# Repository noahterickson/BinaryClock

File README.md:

BinaryClock
===========

A binary clock design

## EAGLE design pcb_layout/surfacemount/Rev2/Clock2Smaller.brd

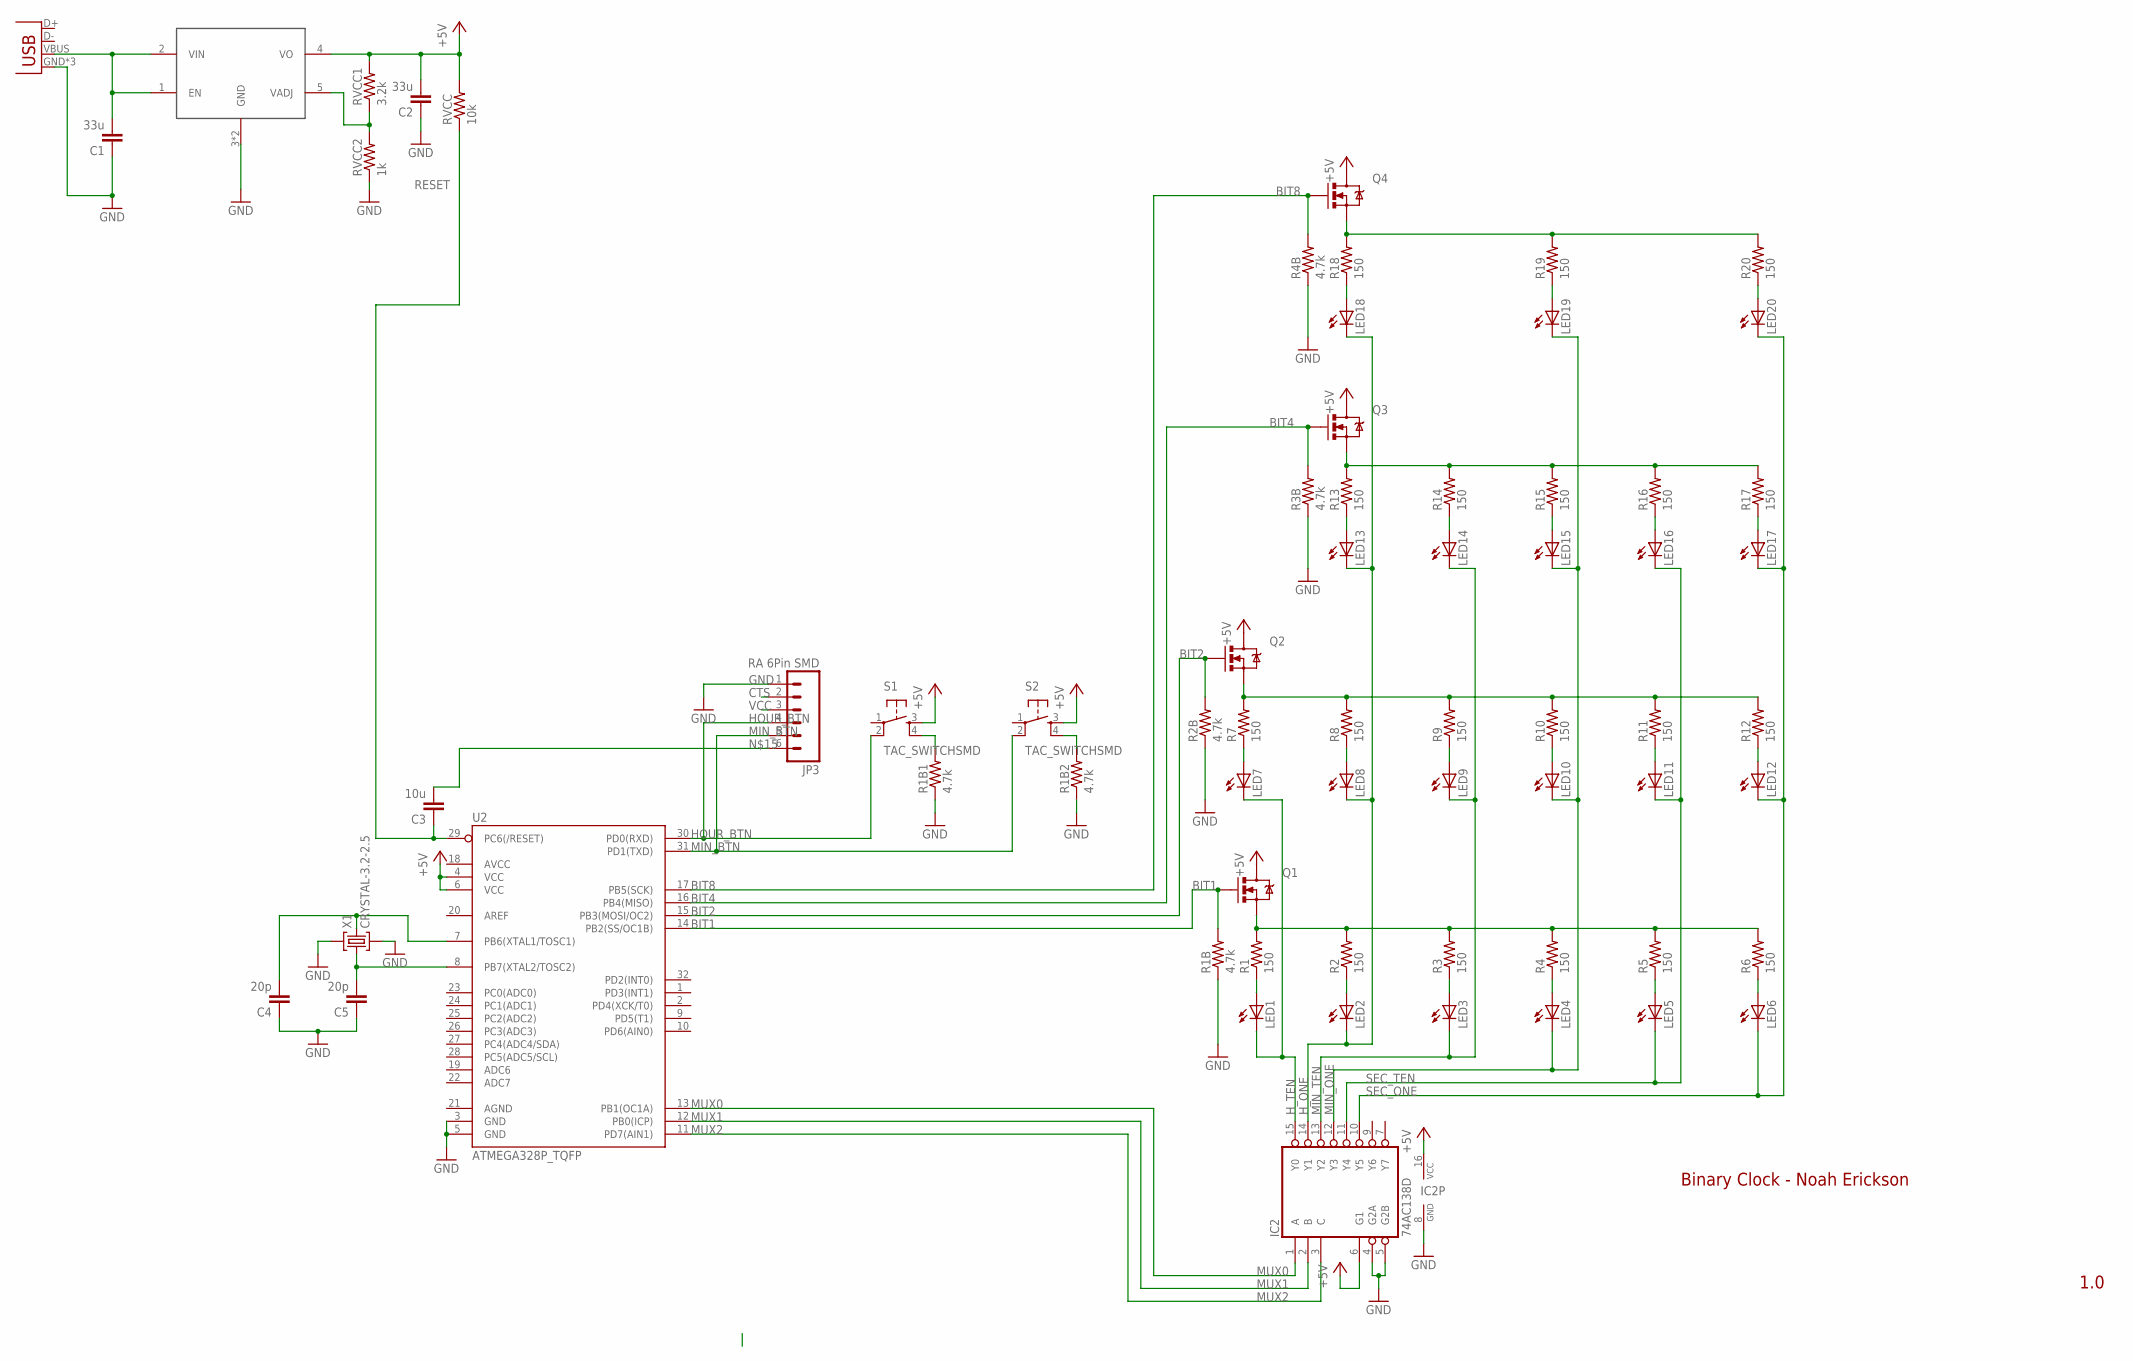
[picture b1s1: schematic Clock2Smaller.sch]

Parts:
C1, C2: 33u; C0805
C3: 10u; C0805
C4, C5: 20p; C0805
IC2: 74AC138D; SO16
JP1: USB-MICROB
JP3: RA 6Pin SMD; 1X06-SMD
LED1, LED2, LED3, LED4, LED5, LED6, LED7, LED8, LED9, LED10, LED11, LED12, LED13, LED14, LED15, LED16, LED17, LED18, LED19, LED20: LEDSML0805; SML0805
Q1, Q2, Q3, Q4: MOSFET-NCHANNELBSS138; SOT23-3
R1, R2, R3, R4, R5, R6, R7, R8, R9, R10, R11, R12, R13, R14, R15, R16, R17, R18, R19, R20: 150; R0805
R1B, R1B1, R1B2, R2B, R3B, R4B: 4.7k; R0805
RVCC: 10k; R0805
RVCC1: 3.2k; R0805
RVCC2: 1k; R0805
S1, S2: TAC_SWITCHSMD; TACTILE-SWITCH-SMD
U2: ATMEGA328P_TQFP; TQFP32-08
U$1: TLF1963; DPAK
X1: CRYSTAL-3.2-2.5

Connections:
+5V: C2.2, IC2.6 (G1), IC2.16 (VCC), Q1.3 (D), Q2.3 (D), Q3.3 (D), Q4.3 (D), RVCC.2, RVCC1.2, S1.3, S2.3, U2.4 (VCC), U2.6 (VCC), U$1.4 (VO)
BIT1: Q1.1 (G), R1B.2, U2.14 (PB2(SS/OC1B))
BIT2: Q2.1 (G), R2B.2, U2.15 (PB3(MOSI/OC2))
BIT4: Q3.1 (G), R3B.2, U2.16 (PB4(MISO))
BIT8: Q4.1 (G), R4B.2, U2.17 (PB5(SCK))
CTS: JP3.2
GND: C1.1, C2.1, C4.1, C5.1, IC2.4 (G2A), IC2.5 (G2B), IC2.8 (GND), JP1.GND, JP1.MT1 (GND), JP1.MT2 (GND), JP3.1, R1B.1, R1B1.1, R1B2.1, R2B.1, R3B.1, R4B.1, RVCC2.1, U2.3 (GND), U2.5 (GND), U$1.3 (GND), U$1.6 (GND), X1.2 (GND), X1.4 (GND)
HOUR_BTN: JP3.4, S1.2, U2.30 (PD0(RXD))
H_ONE: IC2.14 (Y1), LED2.C, LED8.C, LED13.C, LED18.C
H_TEN: IC2.15 (Y0), LED1.C, LED7.C
MIN_BTN: JP3.5, S2.2, U2.31 (PD1(TXD))
MIN_ONE: IC2.12 (Y3), LED4.C, LED10.C, LED15.C, LED19.C
MIN_TEN: IC2.13 (Y2), LED3.C, LED9.C, LED14.C
MUX0: IC2.1 (A), U2.13 (PB1(OC1A))
MUX1: IC2.2 (B), U2.12 (PB0(ICP))
MUX2: IC2.3 (C), U2.11 (PD7(AIN1))
unnamed: C1.2, JP1.VBUS, U$1.1 (EN), U$1.2 (VIN)
unnamed: C5.2, U2.8 (PB7(XTAL2/TOSC2)), X1.1 (C1)
unnamed: C4.2, U2.7 (PB6(XTAL1/TOSC1)), X1.3 (C2)
unnamed: Q4.2 (S), R18.2, R19.2, R20.2
unnamed: LED1.A, R1.1
unnamed: Q1.2 (S), R1.2, R2.2, R3.2, R4.2, R5.2, R6.2
unnamed: R1B1.2, S1.4
unnamed: R1B2.2, S2.4
unnamed: LED2.A, R2.1
unnamed: RVCC1.1, RVCC2.2, U$1.5 (VADJ)
unnamed: C3.2, JP3.6
unnamed: LED3.A, R3.1
unnamed: LED7.A, R7.1
unnamed: Q2.2 (S), R7.2, R8.2, R9.2, R10.2, R11.2, R12.2
unnamed: LED8.A, R8.1
unnamed: LED13.A, R13.1
unnamed: LED9.A, R9.1
unnamed: Q3.2 (S), R13.2, R14.2, R15.2, R16.2, R17.2
unnamed: LED4.A, R4.1
unnamed: LED5.A, R5.1
unnamed: LED18.A, R18.1
unnamed: LED6.A, R6.1
unnamed: LED10.A, R10.1
unnamed: LED11.A, R11.1
unnamed: LED12.A, R12.1
unnamed: LED14.A, R14.1
unnamed: LED15.A, R15.1
unnamed: LED19.A, R19.1
unnamed: LED16.A, R16.1
unnamed: LED17.A, R17.1
unnamed: LED20.A, R20.1
RESET: C3.1, RVCC.1, U2.29 (PC6(/RESET))
SEC_ONE: IC2.10 (Y5), LED6.C, LED12.C, LED17.C, LED20.C
SEC_TEN: IC2.11 (Y4), LED5.C, LED11.C, LED16.C
VCC: JP3.3

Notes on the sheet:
Binary Clock - Noah Erickson
1.0

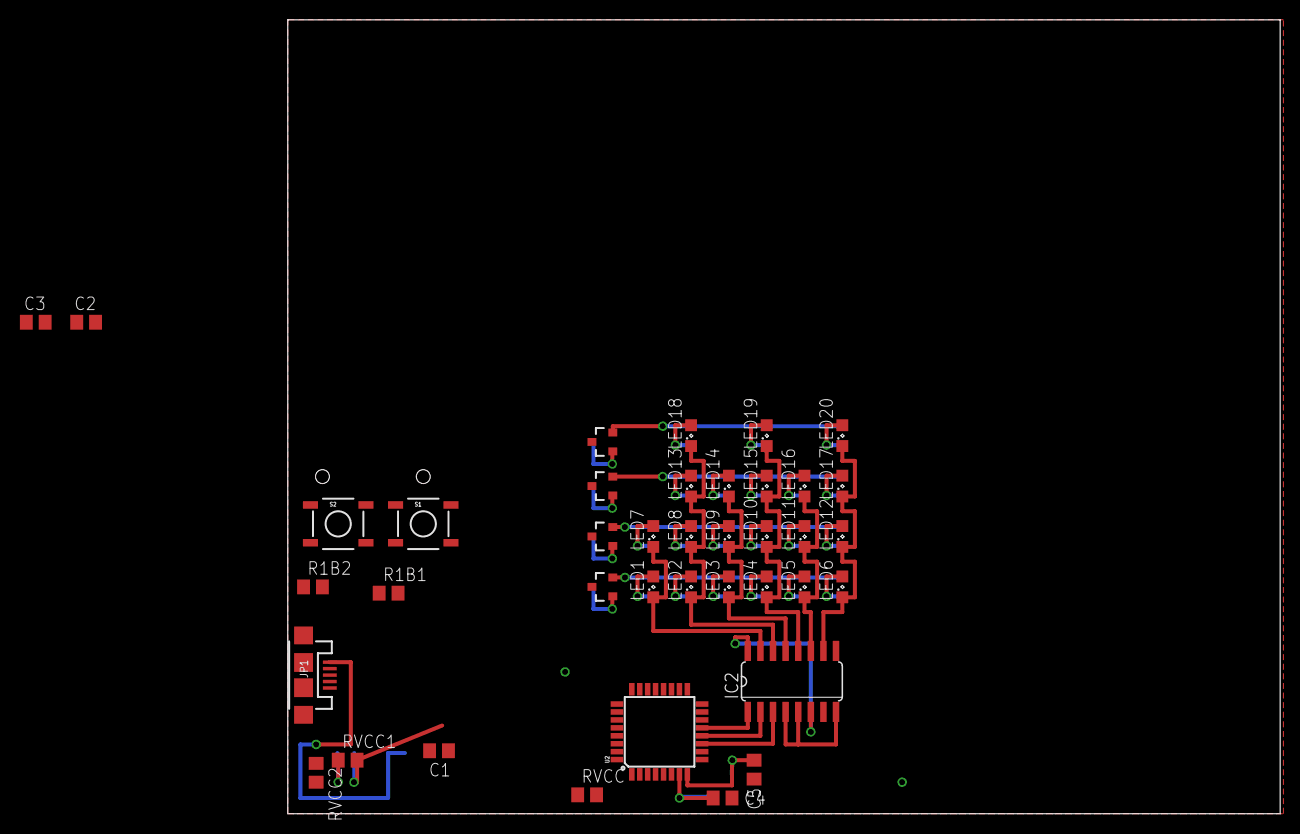
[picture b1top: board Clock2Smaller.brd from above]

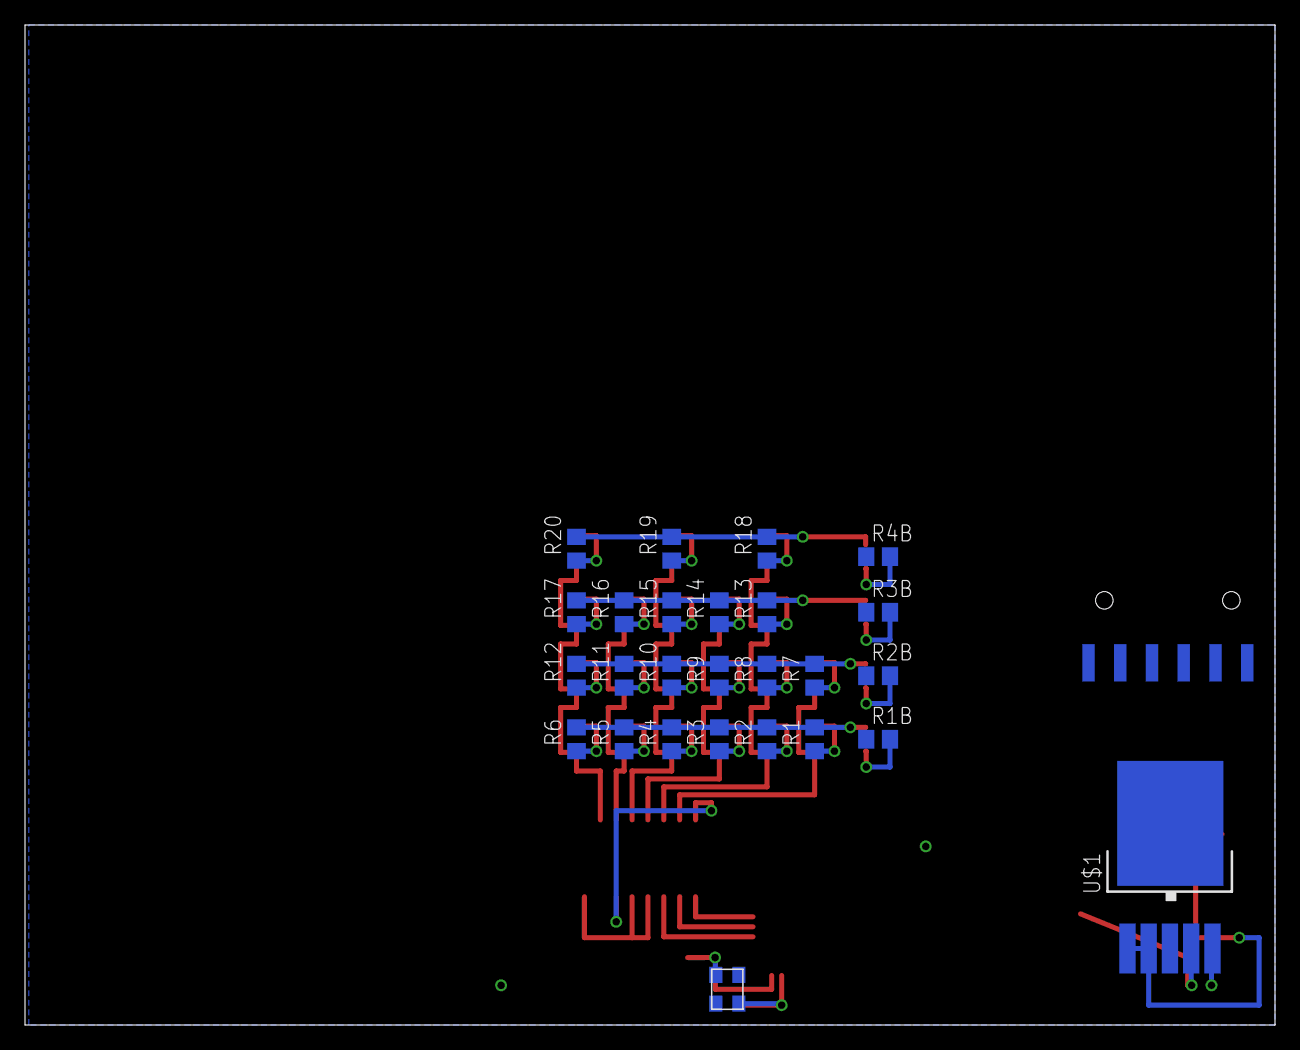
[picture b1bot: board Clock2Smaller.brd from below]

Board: 2 copper layers, 100.0 x 80.0 mm, 66 parts (27 on the bottom side), 49 nets.

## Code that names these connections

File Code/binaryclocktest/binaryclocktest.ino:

/*
Inspired by sbbrain from instructables.com
http://www.instructables.com/id/Full-Binary-Clock/step6/The-Code/
*/

#define mux0 9 //arduino pin 9, atmega pin 15
#define mux1 8 //arduino pin 8, atmega pin 14
#define mux2 7 //arduino pin 7, atmega pin 13

#define bit1 10 //arduino pin 10, atmega pin 16
#define bit2 11 //arduino pin 11, atmega pin 17
#define bit4 12 //arduino pin 12, atmega pin 18
#define bit8 13 //arduino pin 13, atmega pin 19
#define hourButton 2 //arduino pin 0, atmega pin 2
#define minButton 3 //arduino pin 1, atmega pin 3

#include <avr/interrupt.h>


// Function that printf and related will use to print
int serial_putchar(char c, FILE* f) {
    if (c == '\n') serial_putchar('\r', f);
    return Serial.write(c) == 1? 0 : 1;
}

FILE serial_stdout;

void setup(){
    Serial.begin(9600);

    // Set up stdout
    fdev_setup_stream(&serial_stdout, serial_putchar, NULL, _FDEV_SETUP_WRITE);
    stdout = &serial_stdout;

  // put your setup code here, to run once:
  // Enable global interrupts
  SREG |= (1 << 7);
  // Interrupt on rising edge for pins 1,0 (pg. 71)
  EICRA |= (1 << ISC11) | (1 << ISC10) | (ISC01) | (ISC00);
  // Enable interrupts on INT0,INT1 (pins 3,4)
  EIMSK |= (1 << INT1) | (1 << INT0);
  
  Serial.begin(9600);
  
  pinMode(hourButton, INPUT);
  pinMode(minButton, INPUT);
  pinMode(mux0, OUTPUT);
  pinMode(mux1, OUTPUT);
  pinMode(mux2, OUTPUT);
  pinMode(bit1, OUTPUT);
  pinMode(bit2, OUTPUT);
  pinMode(bit4, OUTPUT);
  pinMode(bit8, OUTPUT);
}

void mux(int muxa2, int muxa1, int muxa0){
  digitalWrite(mux0, muxa0);
  digitalWrite(mux1, muxa1);
  digitalWrite(mux2, muxa2);
  
}

int secOne=1, minOne=3, hourOne=0;
int secTen=1, minTen=2, hourTen=0;
int configTime = 1000; //260 seems about right for simulation, 1000 for circuit?

ISR(INT0_vect) {
  hourOne++;
}

ISR(INT1_vect) {
  minOne++;
}

void columns(int columnNum)
{
  byte one;
  byte two;
  byte four;
  byte eight;
  
  switch (columnNum) {
  case 0: //for secOnes
      if (secOne == 1 || secOne == 3 || secOne == 5 || secOne == 7 || secOne == 9) {
        one = HIGH;
      }
      else {
        one = LOW;
      }
      if (secOne == 2 || secOne == 3 || secOne == 6 || secOne == 7) {
        two = HIGH;
      }
      else {
        two = LOW;
      }
      if (secOne == 4 || secOne == 5 || secOne == 6 || secOne == 7) {
        four = HIGH;
      }
      else {
        four = LOW;
      }
      if (secOne == 8 || secOne == 9) {
        eight = HIGH;
      }
      else {
        eight = LOW;
      }
      if (secOne == 0) {
        one = LOW;
        two = LOW;
        four = LOW;
        eight = LOW;
      }
      row(one,two,four,eight);
      break;
  case 1: //for secTens
      if (secTen == 1 || secTen == 3 || secTen == 5 || secTen == 7 || secTen == 9) {
        one = HIGH;
      }
      else {
        one = LOW;
      }
      if (secTen == 2 || secTen == 3 || secTen == 6 || secTen == 7) {
        two = HIGH;
      }
      else {
        two = LOW;
      }
      if (secTen == 4 || secTen == 5 || secTen == 6 || secTen == 7) {
        four = HIGH;
      }
      else {
        four = LOW;
      }
      if (secTen == 8 || secTen == 9) {
        eight = HIGH;
      }
      else {
        eight = LOW;
      }
      if (secTen == 0) {
        one = LOW;
        two = LOW;
        four = LOW;
        eight = LOW;
      }
      row(one,two,four,eight);
      break;
  case 2: //for minOnes
      if (minOne == 1 || minOne == 3 || minOne == 5 || minOne == 7 || minOne == 9) {
        one = HIGH;
      }
      else {
        one = LOW;
      }
      if (minOne == 2 || minOne == 3 || minOne == 6 || minOne == 7) {
        two = HIGH;
      }
      else {
        two = LOW;
      }
      if (minOne == 4 || minOne == 5 || minOne == 6 || minOne == 7) {
        four = HIGH;
      }
      else {
        four = LOW;
      }
      if (minOne == 8 || minOne == 9) {
        eight = HIGH;
      }
      else {
        eight = LOW;
      }
      if (minOne == 0) {
        one = LOW;
        two = LOW;
        four = LOW;
        eight = LOW;
      }
      row(one,two,four,eight);
      break;    
  case 3: //for minTens
      if (minTen == 1 || minTen == 3 || minTen == 5 || minTen == 7 || minTen == 9) {
        one = HIGH;
      }
      else {
        one = LOW;
      }
      if (minTen == 2 || minTen == 3 || minTen == 6 || minTen == 7) {
        two = HIGH;
      }
      else {
        two = LOW;
      }
      if (minTen == 4 || minTen == 5 || minTen == 6 || minTen == 7) {
        four = HIGH;
      }
      else {
        four = LOW;
      }
      if (minTen == 8 || minTen == 9) {
        eight = HIGH;
      }
      else {
        eight = LOW;
      }
      if (minTen == 0) {
        one = LOW;
        two = LOW;
        four = LOW;
        eight = LOW;
      }
      row(one,two,four,eight);
      break;
  case 4: //for hours one
      if (hourOne == 1 || hourOne == 3 || hourOne == 5 || hourOne == 7 || hourOne == 9) {
        one = HIGH;
      }
      else {
        one = LOW;
      }
      if (hourOne == 2 || hourOne == 3 || hourOne == 6 || hourOne == 7) {
        two = HIGH;
      }
      else {
        two = LOW;
      }
      if (hourOne == 4 || hourOne == 5 || hourOne == 6 || hourOne == 7) {
        four = HIGH;
      }
      else {
        four = LOW;
      }
      if (hourOne == 8 || hourOne == 9) {
        eight = HIGH;
      }
      else {
        eight = LOW;
      }
      if (hourOne == 0) {
        one = LOW;
        two = LOW;
        four = LOW;
        eight = LOW;
      }
      row(one,two,four,eight);
      break;
  case 5: //for hourTens
      if (hourTen == 1 || hourTen == 3 || hourTen == 5 || hourTen == 7 || hourTen == 9) {
        one = HIGH;
      }
      else {
        one = LOW;
      }
      if (hourTen == 2 || hourTen == 3 || hourTen == 6 || hourTen == 7) {
        two = HIGH;
      }
      else {
        two = LOW;
      }
      if (hourTen == 4 || hourTen == 5 || hourTen == 6 || hourTen == 7) {
        four = HIGH;
      }
      else {
        four = LOW;
      }
      if (hourTen == 8 || hourTen == 9) {
        eight = HIGH;
      }
      else {
        eight = LOW;
      }
      if (hourTen == 0) {
        one = LOW;
        two = LOW;
        four = LOW;
        eight = LOW;
      }
      row(one,two,four,eight);
      break;            
  }
   
}

void showTime(){
  int temp = 10;
  mux(1,1,1); //turn off
  row(0,0,0,0);
  delayMicroseconds(temp);
  
  mux(0,0,0); // for hours, tens
  columns(5);
  delayMicroseconds(temp);

  mux(1,1,1); //turn off
  row(0,0,0,0);
  delayMicroseconds(temp);
  
  mux(0,0,1); //for hours, ones
  columns(4);
  delayMicroseconds(temp);

  mux(1,1,1); //turn off
  row(0,0,0,0);
  delayMicroseconds(temp);
  
  mux(0,1,0); //for minutes tens
  columns(4);
  delayMicroseconds(temp);

  mux(1,1,1); //turn off
  row(0,0,0,0);
  delayMicroseconds(temp);
  
  mux(0,1,1); //for minutes ones
  columns(2);
  delayMicroseconds(temp);

  mux(1,1,1); //turn off
  row(0,0,0,0);
  delayMicroseconds(temp);
  
  mux(1,0,0); //for seconds tens
  columns(1);
  delayMicroseconds(temp);

  mux(1,1,1); //turn off
  row(0,0,0,0);
  delayMicroseconds(temp);
  
  mux(1,0,1); //for seconds ones
  columns(0);
  delayMicroseconds(temp); 
    
}

void row(byte one1, byte two2, byte four4, byte eight8){
  digitalWrite(bit1, one1);
  digitalWrite(bit2, two2);
  digitalWrite(bit4, four4);
  digitalWrite(bit8, eight8);
}

void loop() {
  
  static unsigned long lastSecond = 0;
  

    
  if (millis() - lastSecond >= configTime) {
    lastSecond = millis();
    printf("%d%d:%d%d:%d%d\n",hourTen, hourOne, minTen, minOne, secTen, secOne);

    secOne++;
    }
 
  
  if (secOne > 9) {
    secTen++;
    secOne = 0;
  }
  
  if (secTen > 5) {
    minOne++;
    secTen = 0;
  }
  
  if (minOne > 9) {
    minTen++;
    minOne = 0;
  }
  
  if (minTen > 5) {
    hourOne++;
    minTen = 0;
  }
  
  if (hourOne > 9) {
    hourTen++;
    hourOne = 0;
  }
  
  if (hourTen == 2 && hourOne > 4) {
    hourTen = 0;
    hourOne = 0;
    
  }
  

  
  showTime();
}

  

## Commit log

2014-11-23 Initial code, pcb layout and enclosure
2014-11-23 For Russell
2014-11-23 Add interrupt code
2014-11-24 Serial Debugging added
2014-11-25 Updated packages
2015-04-03 test commit
2015-04-11 Surface mount stuff
2015-04-21 board update

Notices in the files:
parts and their libraries:
SparkFun-Connectors: Licensing: Creative Commons ShareAlike 4.0 International - https://creativecommons.org/licenses/by-sa/4.0
